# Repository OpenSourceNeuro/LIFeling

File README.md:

<p align="left">

<h1 align="center"> LIFeling </h1></p>
<h3 align="center">  An analog LIF/AdEx “silicon neuron” for teaching & exploration</h3></p>
<p align="center"><h6 align="right">developed by M.J.Y. Zimmermann, A. Koumoundourou</h6></p>

<br></br>

## What is LIFeling
<div>
<p style='text-align: justify;'>
LIFeling is a low-cost, through-hole–friendly analog circuit that emulates a spiking neuron in real time. It implements the Leaky Integrate-and-Fire (LIF) and Adaptive Exponential Integrate-and-Fire (AdEx) dynamics using op-amps, RC networks, comparators, and simple transistor/MOSFET logic.

<p style='text-align: justify;'>
Students can turn knobs (capacitance, leak, synaptic gains, adaptation, threshold, reset) and immediately see how membrane voltage and spikes change—just like a patch-clamp demo, but on an interactive PCB.
</p>

<p style='text-align: justify;'>
LIFeling lives alongside our digital <a href="https://github.com/OpenSourceNeuro/Spikeling">Spikeling</a>: project; where Spikeling runs code, LIFeling is purely analog, making the math–to–hardware mapping very explicit. (For background on AdEx/LIF and neuromorphic “silicon neurons”, <a href="https://www-sop.inria.fr/members/Mathieu.Desroches/teaching/MTSN/Articles/Brette_Gertsner_JNeurophysiol_2005.pdf?utm_source=chatgpt.com">See the references</a>).
</p>

<p style='text-align: justify;'>

This project is licensed under the [GNU General Public License v3.0](https://github.com/OpenSourceNeuro/Spikeling-V2/blob/main/LICENSE)<br>
The hardware is licensed under the [CERN OHL v1.2](https://github.com/OpenSourceNeuro/Spikeling-V2/blob/main/PCB%20-%202.2c/LICENSE)
</p>
</div>

<br>

***

## Objectives
- **Pedagogy** first: Make classical neuron equations tangible with knobs, LEDs, and BNC/TTL I/O so learners can fit parameters from data and build intuition.

- **Open, repairable, reproducible**: THT-preferred BOM where possible; common op-amps (e.g., MCP6004), LM339-class comparators, simple passives; documented test procedures.

- **Immediate feedback**: Real-time dynamics without sampling/latency; scope-friendly nodes for Vm, synaptic currents, threshold comparator, adaptation current.

- **Bridging models**: Start with LIF; switch in AdEx features (exp spike term + adaptation) to show how richer behaviours emerge with just a few components.

- **Teaching exercises**: Provide ready-to-run lab activities (τm measurement, I–F curves, refractory period, synaptic summation, adaptation fitting, noise & reliability). (See Exercises below.)

- **Interoperability**: Optional headers/IO for stimulus/recording from microcontrollers (ESP32/Arduino) and classroom oscilloscopes.

## The models LIFeling implements

#### 1) Leaky Integrate-and-Fire (LIF)

```math
C_m * dV/dt = -g_L * (V - E_L) + I_syn(t) + I_inj(t) - w(t)
```

If V >= V_th  ⇒  V ← V_reset  and hold for τ_ref

with synaptic drive typically modeled as:

```math
I_syn(t) = Σ_i g_i(t) * (E_i - V)
```

LIF captures integration, leakage, threshold, reset, and refractory with minimal parameters.

### Adaptive Exponential Integrate-and-Fire (AdEx)

```math
C_m * dV/dt = -g_L * (V - E_L)
              + g_L * Δ_T * exp((V - V_T)/Δ_T)
              - w
              + I_syn(t) + I_inj(t)

τ_w * dw/dt = a * (V - E_L) - w

If V >= V_spike  ⇒  V ← V_reset  and  w ← w + b
```

AdEx adds a soft, exponential spike-initiation term and an adaptation state w, reproducing rich firing patterns with few parameters.

- Further reading: Brette & Gerstner 2005 (AdEx); Dayan & Abbott 2001 (LIF fundamentals); Indiveri et al. 2011 (neuromorphic neuron circuits).

## Circuit ↔ equation map

| Equation term | Biological meaning | Circuit element(s) | What to adjust / observe |
|---|---|---|---|
| `C_m` | Membrane capacitance (area/biophysics) | Selectable capacitor bank; front-panel selector | Larger `C_m` → slower `V_m` dynamics; measure a step response to estimate `τ_m = C_m / g_L`. |
| `g_L`, `E_L` | Leak conductance & resting potential | Potentiometer or resistor ladder to ground/bias; optional reference sets `E_L` | Increasing `g_L` lowers input resistance and shortens `τ_m`; trimming `E_L` shifts the baseline. |
| `I_syn = Σ g_i(t) · (E_i − V)` | Synaptic drive (EPSC/IPSC) with reversal | 4× synapse shapers (RC) with gain/polarity pots; bias selects excitatory vs inhibitory | Temporal summation, shunting inhibition; switch time constants (fast/slow) to compare PSP shapes. |
| `Δ_T`, `V_T` | Spike-onset sharpness & soft threshold (AdEx) | Exponential I–V subcircuit (diode/transconductance shaping) feeding the membrane node | Increase `Δ_T` for smoother onset; adjust `V_T` to shift effective threshold and excitability. |
| `w`, `a`, `b`, `τ_w` | Adaptation current and kinetics | Slow RC + transconductance; spike-triggered charge increment into `w` | Fit `a`, `b`, `τ_w` from step protocols; observe spike-frequency adaptation and after-spike effects. |
| Spike detect & reset | Action potential event and absolute refractory | LM339-class comparator → MOSFET/analog switch clamp to `V_reset`; monostable sets `τ_ref` | Tune `V_th`, `V_reset`, `τ_ref`; verify with ISI histograms and two-pulse tests. |
| `I_inj` | Current clamp / external stimulus | BNC/3.5 mm input, on-board button, or photodiode path | Use steps/ramps/noise to probe `f–I` curves, threshold, reliability, and dynamic range. |

## Biological correspondence: what’s faithful vs abstracted

Faithful: passive membrane (R–C), synaptic time courses (first-order), EPSP/IPSP summation, threshold/reset phenomenology, refractory period, spike-frequency adaptation.

Abstracted: no detailed action-potential waveform (we model its effect via threshold/reset); ion-channel kinetics are lumped into **g_L**, the exponential term, and **w** rather than Hodgkin–Huxley-style gates.

Optional background: when teaching resting potentials and synaptic reversal, connect channel-specific reversal potentials **E_i** to Nernst/GHK equations (see References).

## Front-panel controls (typical)

**Membrane**: C_m selector, Leak pot (g_L), E_L trim.

**Synapses (×4)**: Gain pot, Polarity switch (E/I), τ_s switch (fast/slow).

**AdEx**: V_T, Δ_T trims (soft threshold), Adaptation (a, b, τ_w) pots.

**Spiking**: V_th, V_reset, τ_ref trims; Spike LED.

**I/O**: Vm out (scope), Spike out (TTL), Stim in (BNC/3.5 mm), light-sensor jack.

Start with τ_m ≈ 5–100 ms and spike thresholds ~0.8–1.8 V relative to your virtual ground (adjust for your supply).

## Quick start (bench)

Power & baseline. Power the board; set all gains mid-range; choose C_m, set leak mid.

Wire the scope. CH1 = Vm; CH2 = Spike TTL.

Elicit spikes. Inject a 0.5–2 s current step; adjust threshold/reset until regular spiking appears.

Add small Δ_T and adaptation (τ_w ≈ 200–500 ms). Watch firing adapt down.

Play with synapses. Use fast EPSPs and slower IPSPs to demonstrate temporal summation and shunting inhibition.

## Suggested classroom exercises

**Measure membrane time constant τ_m.**
Inject a small subthreshold step; fit V(t) = E_L + ΔV*(1 - exp(-t/τ_m)). Recover C_m or g_L and compare to knob settings.

**I–F (f–I) curve & rheobase.**
Ramp I_inj and record firing rate. Fit slope and rheobase; show how g_L and C_m change slope/offset.

**Refractory period.**
Deliver two pulses separated by Δt; find minimum Δt producing two spikes; compare to τ_ref.

**Synaptic summation and shunting.**
Pair an EPSP with a near-coincident IPSP; demonstrate divisive gain control by increasing inhibitory conductance (shunting).

**Spike-frequency adaptation (AdEx).**
Step-current protocol; fit a, b, τ_w from the early/late rates and the post-spike adaptation jump.

**Soft vs hard threshold.**
Compare LIF (hard V_th) to AdEx (Δ_T > 0). Show smoother onset and different ISI variability with AdEx.

**Noise & reliability.**
Add small noise to I_inj; plot spike-time jitter vs g_L. Discuss reliability/variability trade-offs.

**Analog vs digital (optional).**
Recreate one exercise on a microcontroller neuron (e.g., Izhikevich) and compare dynamics, latency, and parameter identifiability.

## Acknowledgments

Foundation: This project is based on Lu.i — https://github.com/giant-axon/lu.i-neuron-pcb

Thanks to the neuromorphic-hardware community for decades of open designs and teaching inspiration.

## References & further reading

AdEx model — Brette, R. & Gerstner, W. (2005). Adaptive Exponential Integrate-and-Fire Model as an Effective Description of Neuronal Activity. Journal of Neurophysiology, 94(5), 3637–3642. https://doi.org/10.1152/jn.00686.2005

LIF & synapses — Dayan, P. & Abbott, L. F. (2001). Theoretical Neuroscience. MIT Press. (See chapters on LIF, synapses, and I–F curves.)

Neuromorphic circuits — Indiveri, G., Linares-Barranco, B., et al. (2011). Neuromorphic Silicon Neuron Circuits. Frontiers in Neuroscience, 5:73. https://doi.org/10.3389/fnins.2011.00073
 (Open access)

Spiking for teaching (digital reference) — Baden, T., James, B., et al. (2018). Spikeling: a low-cost hardware implementation of a spiking neuron for neuroscience teaching and outreach. PLOS Biology. https://doi.org/10.1371/journal.pbio.2006760

Ion channels & reversals (background) — Hille, B. (2001). Ion Channels of Excitable Membranes (3rd ed.). Sinauer. (Nernst/GHK chapters)

## Contributing

Issues and PRs welcome!
When reporting results, please include:

Scope captures (Vm & Spike TTL),

Knob settings (Cm, gL, ΔT, Vth, Vreset, τref, a, b, τw),

The stimulus used (step amplitude, duration, ramp slope, synaptic timing),

Supply voltage and any modifications to the reference design.

## FAQ

Is this a “real” action potential?
No—the analog spike is implicit (threshold/reset). That’s by design and matches reduced-model pedagogy.

Why analog instead of a microcontroller?
Zero-latency dynamics and a literal circuit-to-equation mapping you can probe with a scope—excellent for intuition building.

Can I add more biology?
Yes: add synapse types (different τ_s), noise sources, or a second compartment. Use the AdEx literature and neuromorphic reviews as guidance.

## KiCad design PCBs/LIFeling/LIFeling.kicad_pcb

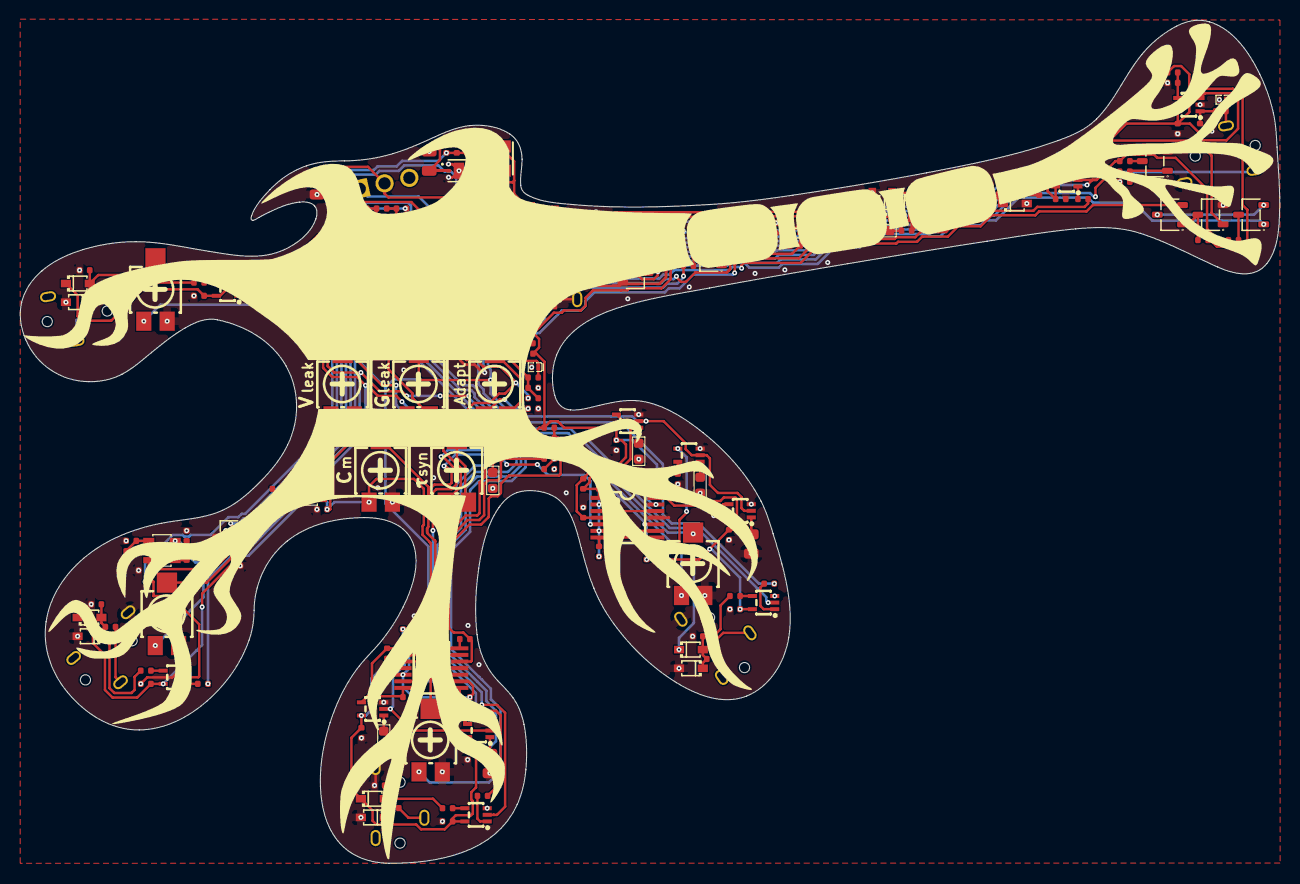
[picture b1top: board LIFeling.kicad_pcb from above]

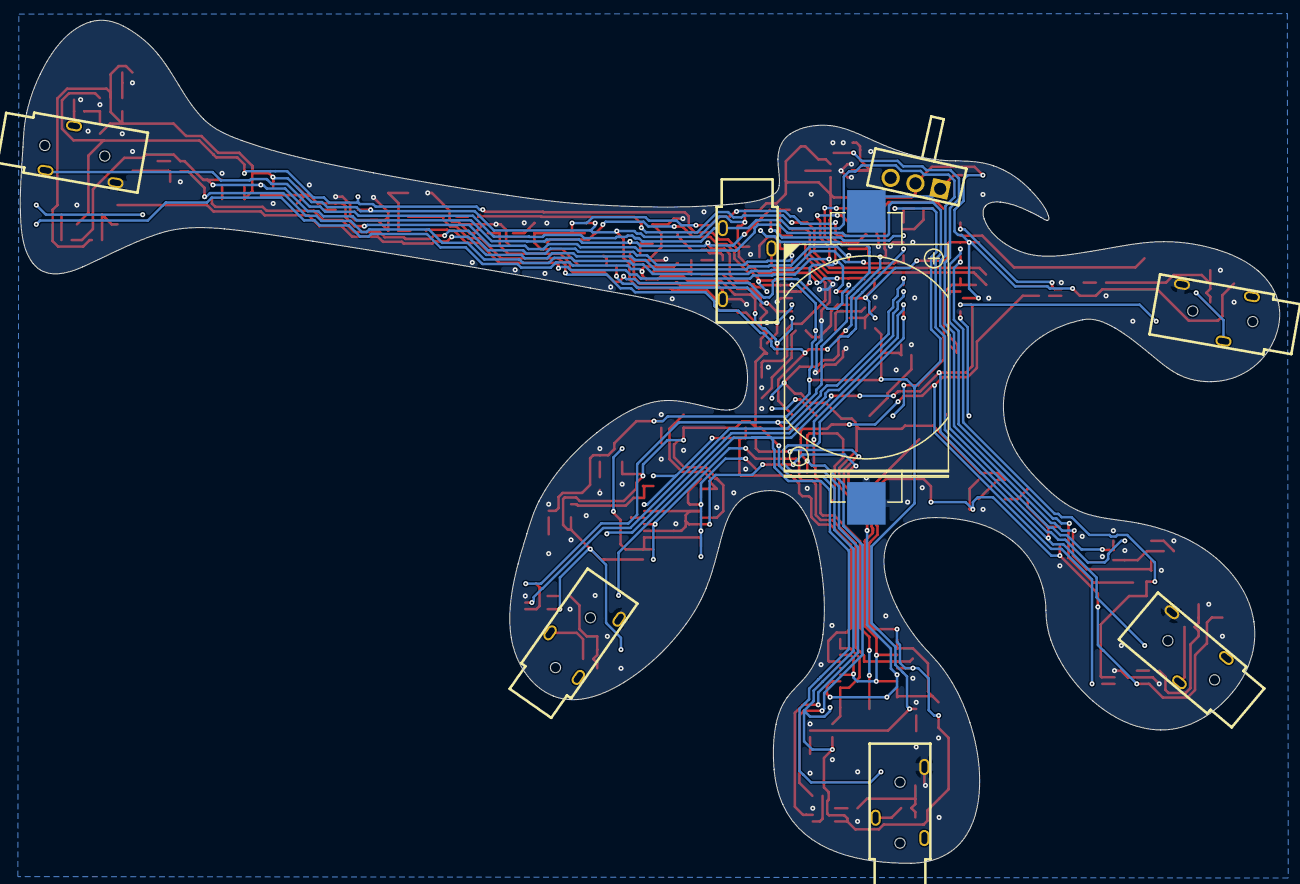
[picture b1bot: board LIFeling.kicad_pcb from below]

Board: 2 copper layers, 124.1 x 83.0 mm, 215 parts (8 on the bottom side), 106 nets.

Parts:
BT1: type="R" model="Battery_Cell" lib=""; BAT-TH_CR2032-BS-6-1
C1, C2, C9, C26, C30: 10uF; C_0805
C3, C4, C5, C6, C7, C8, C12, C14, C15, C17, C19, C21, C23, C25, C27, C32, C34, C35, C36, C37, C40, C41, C42: 100nF; C_0402
C10: 22uF; C_0805
C11, C33: 1uF; C_0402
C13, C28, C39: 100pF; C_0402
C16: 22nF; C_0402
C18: 470nF; C_0603
C20, C29: 1uF; C_0603
C22: 2.2uF; C_0603
C24: 4.7uF; C_0805
C31: 10nF; C_0402
C38: 220nF; C_0603
D1, D19: TPD1E05U06DPYT; X1SON-2_L1.0-W0.6-P0.65-RD-1
D2, D3, D10, D11, D12, D13, D14, D15, D16, D17, D21, D22: BAT54WS L9; SOD-323_L1.8-W1.3-LS2.5-RD
D4, D5, D7: 1N4148WS; SOD-323_L1.8-W1.3-LS2.5-RD-1
D6, D8, D20: RB521S30T1G; SOD-523_L1.2-W0.8-LS1.6-RD
D9: 19-237/R6GHBHC-A01/2T; LED-SMD_4P-L1.6-W1.6-19-237A-BHR6GHC-A01-2T
D18: TPD1E05U06DPYT; X1SON-2_L1.0-W0.6-P0.65-RD
H1, H2, H3, H4, H5, H6: MountingHole; MountingHole_2.2mm_M2
J1: Stim_Ext; AUDIO-SMD_HX-PJ-320A-3P-DIP
J2: Axon_Output; AUDIO-SMD_HX-PJ-320A-3P-DIP
J3: Syn1_Input; AUDIO-SMD_HX-PJ-320A-3P-DIP
J4: Syn2_Input; AUDIO-SMD_HX-PJ-320A-3P-DIP
J5: Syn3_Input; AUDIO-SMD_HX-PJ-320A-3P-DIP
J6: Syn4_Input; AUDIO-SMD_HX-PJ-320A-3P-DIP
L1: 2.2uH; IND-SMD_L3.0-W3.0_SMNR3015
Q1, Q3, Q4, Q5, Q6, Q7: BSS138; SOT-23-3_L2.9-W1.6-P1.90-LS2.8-BR
Q2, Q8: MMBT3904; SOT-23-3_L2.9-W1.6-P1.90-LS2.8-BR
R1: 10Ω; R_0402
R2: 220Ω; R_0402
R3, R16, R37, R46, R52, R60, R64, R82: 10kΩ; R_0402
R4, R8, R9, R11, R15, R17, R18, R19, R20, R21, R22, R24, R27, R30, R33, R38, R42, R43, R48, R49, R51, R55, R59, R65, R68, R72, R76, R80, R88, R92, R95, R96, R97: 100kΩ; R_0402
R5, R6, R13, R14, R58: 220kΩ; R_0402
R7: 20kΩ; R_0402
R10: 56kΩ; R_0402
R12, R23, R25, R26, R28, R29, R31, R32, R34, R50, R57, R83, R84, R85, R86, R90: 1MΩ; R_0402
R35, R67, R71, R75, R79, R91: 1kΩ; R_0402
R36: 2.2MΩ; R_0402
R39, R47, R53, R66, R69, R70, R73, R74, R77, R78, R81: 22kΩ; R_0402
R40, R54, R89: 100Ω; R_0402
R41, R44, R93, R94: 200kΩ; R_0402
R45: 330kΩ; R_0402
R56: 270kΩ; R_0402
R61, R62, R63: 2kΩ; R_0402
R87: 47kΩ; R_0402
RV1, RV3, RV4, RV5: 100kΩ; RES-ADJ-SMD_G43BT
RV2: 50kΩ; RES-ADJ-SMD_G43BT
RV6, RV7, RV8, RV9: 1MΩ; RES-ADJ-SMD_G43BT
SW1: K3-1260D-L1; SW-TH_K3-1260D-L1
U1, U2, U3: MCP6004T-I/ST; TSSOP-14_L5.0-W4.4-P0.65-LS6.4-BL
U4, U5, U6: TLV7044PWR; TSSOP-14_L5.0-W4.4-P0.65-LS6.4-BL
U7: TPS610995DRVR; WSON-6_L2.0-W2.0-P0.65-TL-EP
U8, U22: TLV9001IDBVR; SOT-23-5_L3.0-W1.7-P0.95-LS2.8-BR
U9, U10, U11, U12, U13, U14, U15, U16, U17, U18, U20: TS5A3166DCKR; SC-70-5_L2.1-W1.3-P0.65-LS2.1-BR
U19: TLV7031DCKR; SC-70-5_L2.1-W1.3-P0.65-LS2.2-BR
U21: REF3020AIDBZR; SOT-23-3_L3.0-W1.7-P0.95-LS2.9-BR

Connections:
+BATT: BT1.1 (+), C1.1, SW1.1
/AP_Gate: Q1.1 (G), R36.2, R37.2, U6.14 (OUTD)
/Adapt: R44.2, R45.1, U2.14 (VOUTD)
/Adapt_Base: Q2.1, R47.1, R48.1
/Adapt_Current_Sink: Q2.3, R46.2
/Adapt_Kick_Drive: C29.2, U2.1 (VOUTA), U2.2 (VINA-)
/Reset_Gated_Drive: Q6.3 (D), R60.1
/Reset_Injection_Drive: Q5.2 (S), U2.6 (VINB-), U2.7 (VOUTB)
/Reset_Injection_Enable: Q4.3 (D), Q5.1 (G), R59.2
/Reset_Switch_Mid: Q5.3 (D), Q6.2 (S)
/Reset_Timer_Discharge: Q3.3 (D), R54.1
/Rising_AP: C31.2, D8.2 (A), R49.1
/V_Leak_ref: RV1.2, U3.3 (VINA+)
/V_Syn_Drive: R86.2, R87.1, U1.14 (VOUTD)
/Vkick: C29.1, D4.1 (C), D5.2 (A), R39.2
AP: C31.1, Q1.3 (D), Q3.1 (G), R38.2, U2.3 (VINA+)
GNDREF: BT1.2 (-), C1.2, C2.2, C3.1, C4.1, C5.1, C6.1, C7.1, C8.1, C9.2, C10.1, C11.2, C12.2, C13.2, C14.2, C15.2, C16.1, C17.2, C18.2, C19.2, C20.2, C21.2, C22.2, C23.2, C24.2, C25.2, C26.2, C27.2, C28.1, C30.1, C32.2, C33.1, C34.2, C35.2, C36.2, C37.2, C38.1, C39.2, C40.2, C41.1, C42.1, D1.2 (GND), D3.2 (A), D4.2 (A), D7.2 (A), D11.2 (A), D13.2 (A), D15.2 (A), D17.2 (A), D18.2 (GND), D19.2 (GND), D20.2 (A), D22.2 (A), J1.3, J2.3, J3.3, J4.3, J5.3, J6.3, Q1.2 (S), Q2.2, Q3.2 (S), Q4.2 (S), Q7.2 (S), Q8.2, R4.1, R6.1, R8.2, R10.1, R12.1, R14.1, R21.2, R39.1, R40.2, R41.1, R48.2, R49.2, R50.1, R58.1, R65.2, R68.1, R72.1, R76.1, R80.1, RV1.1, RV4.1, RV6.1, RV7.1, RV8.1, RV9.1, U1.11 (VSS), U2.11 (VSS), U3.11 (VSS), U4.11 (VEE), U5.11 (VEE), U6.11 (VEE), U7.1 (GND), U7.3 (FB), U7.7 (PowerPad), U8.2 (V-), U9.3 (GND), U10.3 (GND), U11.3 (GND), U12.3 (GND), U13.3 (GND), U14.3 (GND), U15.3 (GND), U16.3 (GND), U17.3 (GND), U18.3 (GND), U19.2 (GND), U20.3 (GND), U21.3 (GND), U22.2 (V-)
unnamed: D6.2 (A), R45.2
unnamed: D9.3 (B-), R61.2
unnamed: D9.2 (G-), R62.2
unnamed: D9.1 (R-), R63.2
unnamed: D10.2 (A), D11.1 (K), R67.2, R68.2, R69.2
unnamed: D12.2 (A), D13.1 (K), R71.2, R72.2, R73.2
unnamed: D14.2 (A), D15.1 (K), R75.2, R76.2, R77.2
unnamed: D16.2 (A), D17.1 (K), R79.2, R80.2, R81.2
unnamed: Q7.3 (D), R61.1, R62.1
unnamed: Q8.1, R64.1, R65.1
unnamed: Q8.3, R63.1
unnamed: R35.1, RV2.1
unnamed: R40.1, RV3.3
unnamed: R82.2, RV5.1, RV5.2
unnamed: RV7.2, U1.5 (VINB+)
unnamed: R83.2, R84.2, U1.12 (VIND+)
unnamed: R85.2, R86.1, U1.13 (VIND-)
unnamed: RV6.2, U1.3 (VINA+)
unnamed: R41.2, R42.1, U2.12 (VIND+)
unnamed: R43.1, R44.1, U2.13 (VIND-)
unnamed: RV8.2, U3.10 (VINC+)
unnamed: RV9.2, U3.12 (VIND+)
unnamed: R92.2, R93.2, U6.5 (INB+)
unnamed: R94.2, R95.2, U6.6 (INB-)
unnamed: R56.1, R57.1, R58.2, U6.10 (INC+)
unnamed: C33.2, R53.2, R54.2, U6.9 (INC-)
unnamed: L1.2, U7.5 (SW)
unnamed: C10.2, R1.1, U7.2 (VOUT)
unnamed: C18.1, U9.1 (NO)
unnamed: C20.1, U10.1 (NO)
unnamed: C22.1, U11.1 (NO)
unnamed: C24.1, U12.1 (NO)
unnamed: C26.1, U13.1 (NO)
unnamed: R52.1, U14.1 (NO)
unnamed: R67.1, U15.4 (IN)
unnamed: R66.1, U15.1 (NO)
unnamed: R71.1, U16.4 (IN)
unnamed: R70.1, U16.1 (NO)
unnamed: R75.1, U17.4 (IN)
unnamed: R74.1, U17.1 (NO)
unnamed: R79.1, U18.4 (IN)
unnamed: R78.1, U18.1 (NO)
unnamed: R88.2, R89.1, U19.1 (OUT)
unnamed: R16.1, U20.1 (NO)
Peak_Window: Q4.1 (G), R51.2, U6.1 (OUTA), U14.4 (IN), U19.3 (IN+), U20.4 (IN)
Reset_Window: Q6.1 (G), Q7.1 (G), R55.2, R57.2, U6.8 (OUTC)
S0: R22.2, R23.2, U4.1 (OUTA), U9.4 (IN)
S1: R24.2, R25.2, R26.2, U4.7 (OUTB), U4.8 (OUTC), U10.4 (IN)
S2: R27.2, R28.2, R29.2, U5.1 (OUTA), U5.7 (OUTB), U11.4 (IN)
S3: R30.2, R31.2, R32.2, U5.8 (OUTC), U5.14 (OUTD), U12.4 (IN)
S4: R33.2, R34.2, U4.14 (OUTD), U13.4 (IN)
Spike_Out: D18.1 (I/O), J2.2, R89.2
Spike_Pulse: D8.1 (C), D20.1 (C), R50.2, U6.2 (INA+)
Stimulus_Ext: D19.1 (I/O), J1.2, R91.1
Syn1_Spike: J3.2, R69.1
Syn2_Spike: J4.2, R73.1
Syn3_Spike: J5.2, R77.1
Syn4_Spike: J6.2, R81.1
T1: R20.2, R21.1, R23.1, R25.1, U4.2 (INA+), U4.6 (INB-)
T2: R19.2, R20.1, R26.1, R28.1, U4.10 (INC+), U5.3 (INA-)
T3: R18.2, R19.1, R29.1, R31.1, U5.5 (INB+), U5.9 (INC-)
T4: R17.2, R18.1, R32.1, R34.1, U4.13 (IND−), U5.12 (IND+)
VDD: C2.1, C3.2, C4.2, C5.2, C6.2, C7.2, C8.2, C9.1, C17.1, C19.1, C21.1, C23.1, C25.1, C27.1, C32.1, C34.1, C35.1, C36.1, C37.1, C40.1, C41.2, C42.2, D2.1 (K), D9.4 (+), D10.1 (K), D12.1 (K), D14.1 (K), D16.1 (K), D21.1 (K), L1.1, R11.1, R13.2, R17.1, R22.1, R24.1, R27.1, R30.1, R33.1, R37.1, R38.1, R51.1, R53.1, R55.1, R56.2, R59.1, R88.1, R96.1, RV4.3, SW1.2, U1.4 (VDD), U2.4 (VDD), U3.4 (VDD), U4.4 (VCC), U5.4 (VCC), U6.4 (VCC), U7.4 (EN), U7.6 (VIN), U9.5 (V+), U10.5 (V+), U11.5 (V+), U12.5 (V+), U13.5 (V+), U14.5 (V+), U15.5 (V+), U16.5 (V+), U17.5 (V+), U18.5 (V+), U19.5 (VCC), U20.5 (V+), U21.1 (IN), U22.5 (V+)
VREF_1V024: R7.2, R9.1, R85.1, R90.1, R94.1, RV5.3, U22.1 (OUT), U22.4 (IN-)
VREF_1V024_RAW: R5.1, R6.2, U22.3 (IN+)
VREF_2V048: C15.1, R5.2, RV6.3, RV7.3, RV8.3, RV9.3, U3.5 (VINB+), U21.2 (OUT)
V_Boost: C11.1, C12.1, C14.1, R1.2, U8.5 (V+)
V_Leak: R43.2, RV2.3, U3.1 (VOUTA), U3.2 (VINA-)
V_Leak_Ref_Max: RV1.3, U3.6 (VINB-), U3.7 (VOUTB)
V_Logic_Mid: R13.1, R14.2, U19.4 (IN-)
V_Peak_Drive: R16.2, R52.2, U2.8 (VOUTC), U2.9 (VINC-)
V_Peak_Ref: R11.2, R12.2, U2.10 (VINC+)
V_Reset_Ref: R9.2, R10.2, U2.5 (VINB+)
V_Stim_Cmd: C39.1, R90.2, R91.2, R93.1
V_Stim_Drive: R95.1, R96.2, R97.1, U6.7 (OUTB)
V_Syn1_Set: U1.1 (VOUTA), U1.2 (VINA-), U15.2 (COM)
V_Syn2_Set: U1.6 (VINB-), U1.7 (VOUTB), U16.2 (COM)
V_Syn3_Set: U3.8 (VOUTC), U3.9 (VINC-), U17.2 (COM)
V_Syn4_Set: U3.13 (VIND-), U3.14 (VOUTD), U18.2 (COM)
V_Syn_State: C38.2, R66.2, R70.2, R74.2, R78.2, R82.1, R83.1
V_Threshold: R7.1, R8.1, R36.1, U6.3 (INA-), U6.12 (IND+)
Vm_Display_In: C16.2, D21.2 (A), D22.1 (K), R15.1, U8.3 (IN+), U20.2 (COM)
Vm_Ext: C13.1, D1.1 (I/O), J1.1, J2.1, R2.2
Vm_FB: R3.1, R4.2, U8.4 (IN-)
Vm_Int: C28.2, D2.2 (A), D3.1 (K), R15.2, R35.2, R42.2, R46.1, R60.2, R64.2, R84.1, R87.2, R92.1, R97.2, RV2.2, U6.13 (IND−), U9.2 (COM), U10.2 (COM), U11.2 (COM), U12.2 (COM), U13.2 (COM), U14.2 (COM)
Vm_Out_DRV: R2.1, R3.2, U8.1 (OUT)
Vsel: RV4.2, U4.3 (INA-), U4.5 (INB+), U4.9 (INC-), U4.12 (IND+), U5.2 (INA+), U5.6 (INB-), U5.10 (INC+), U5.13 (IND−)
Vw: C30.2, D5.1 (C), D6.1 (C), D7.1 (C), RV3.1, RV3.2, U1.10 (VINC+)
Vw_buff: R47.2, U1.8 (VOUTC), U1.9 (VINC-)

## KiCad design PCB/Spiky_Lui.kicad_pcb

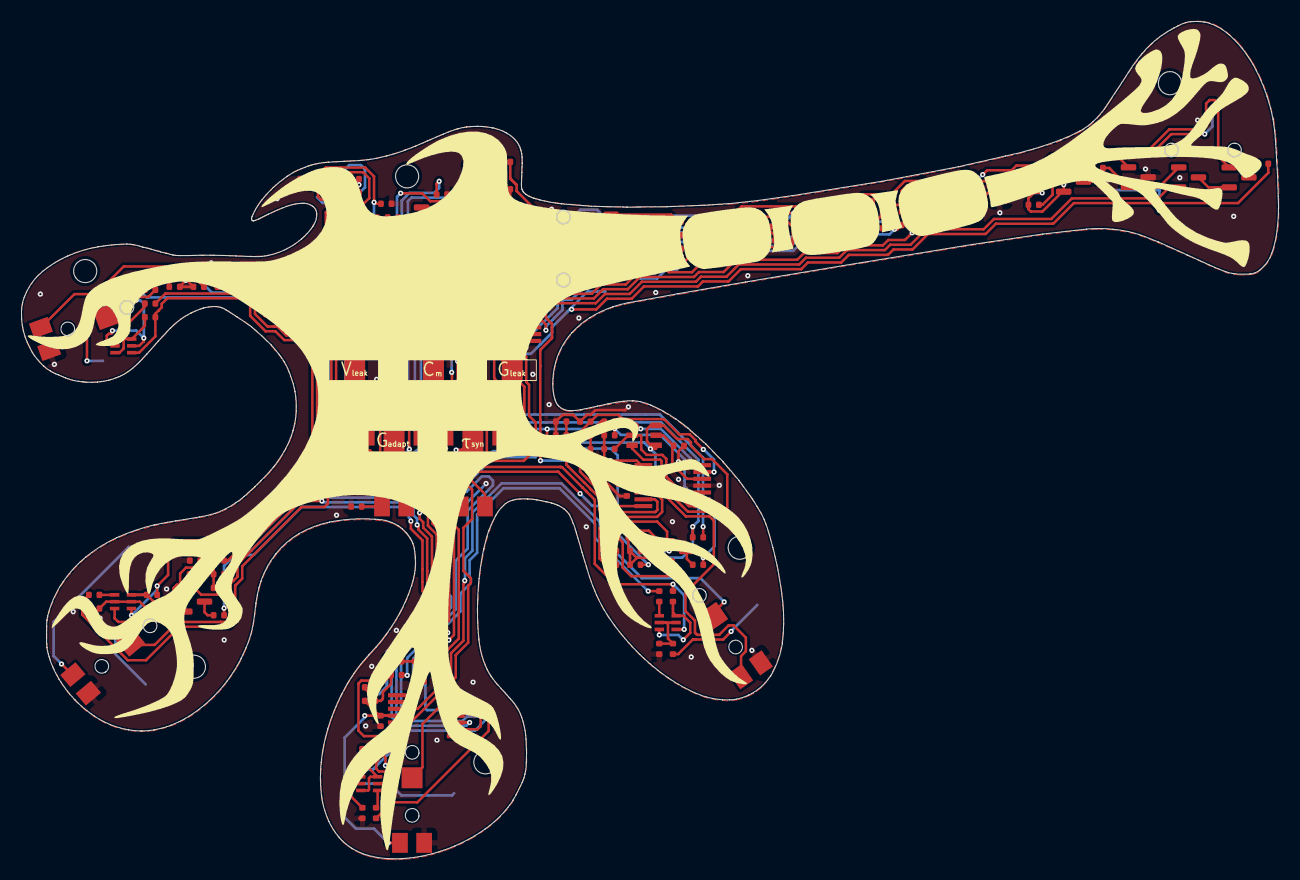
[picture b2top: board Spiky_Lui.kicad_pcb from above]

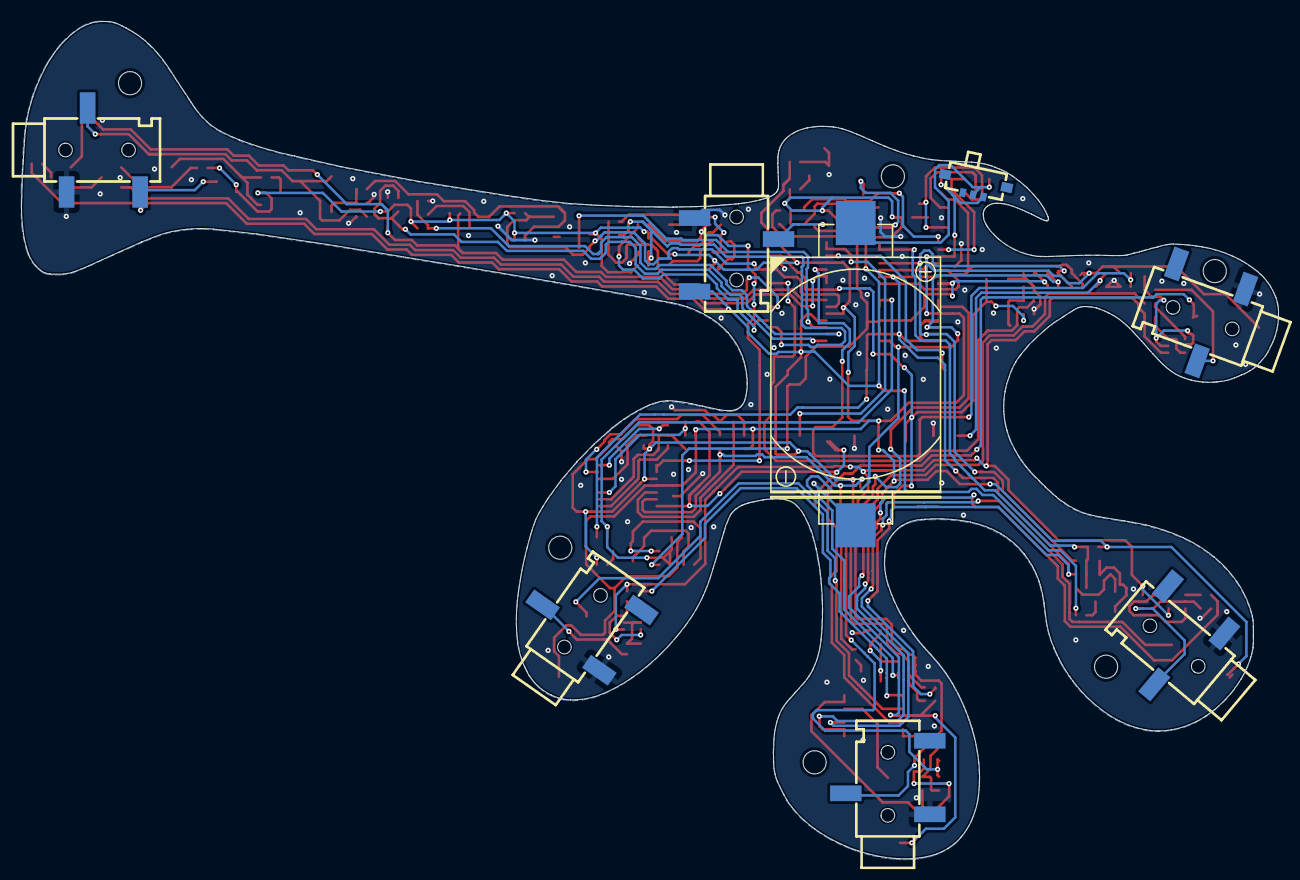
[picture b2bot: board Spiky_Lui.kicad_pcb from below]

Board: 2 copper layers, 119.7 x 79.7 mm, 166 parts (8 on the bottom side), 99 nets.

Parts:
BT1: type="R" model="Battery_Cell" lib=""; BAT-TH_CR2032-BS-6-1
C2: 470nF; C_0402
C3, C14, C16, C17: 1uF; C_0402
C4: 2.2uF; C_0402
C5: 4.7uF; C_0402
C6, C8, C18: 10uF; C_0402
C9, C10, C11, C12, C15, C19, C20: 100nF; C_0402
C13: 10nF; C_0402
D1: 1N4148W; SOD-123_L2.8-W1.8-LS3.7-RD
D2: 19-237/R6GHBHC-A01/2T; LED-SMD_4P-L1.6-W1.6-19-237A-BHR6GHC-A01-2T
D3, D4, D5: 1N4148WS; D_SOD-323
H1, H2, H3, H4, H5, H6: MountingHole; MountingHole_2.2mm_M2
J1: Oscilloscope Jack; AUDIO-SMD_PJ-320B
J2: Axon Output; AUDIO-SMD_PJ-320B
J3: Syn1 Input; AUDIO-SMD_PJ-320B
J4: Syn2 Input; AUDIO-SMD_PJ-320B
J5: Syn3 Input; AUDIO-SMD_PJ-320B
J6: Syn4 Input; AUDIO-SMD_PJ-320B
Q1, Q2, Q3, Q6, Q7, Q16, Q17, Q18, Q19, Q20: N_MOSFET; SOT-23
Q4, Q5: P_MOSFET; SOT-23
Q8: SI3552DV-T1-E3; TSOP-6_L3.0-W1.5-P0.95-BL
Q9, Q10, Q11, Q12: SI1926DL-T1-E3; SOT-363-6_L2.0-W1.3-P0.65-LS2.1-BL
Q13, Q14: MMBT2222A; Q_SOT-23
Q15: MMBT3904; SOT-23
R1: 6.8kΩ; R_0402
R2, R3: 1kΩ; R_0402
R4: 2kΩ; R_0402
R5, R7, R56, R57, R58: 220kΩ; R_0402
R6, R34, R35: 47kΩ; R_0402
R8, R60, R62, R63: 10kΩ; R_0402
R9, R15, R18, R22, R23, R31, R32, R33, R36: 22kΩ; R_0402
R10, R12, R14, R19, R21, R24, R28, R29, R30, R40, R44, R48, R52, R59, R65, R66, R68, R70, R72, R76, R79, R80, R83, R86, R89, R92: 100kΩ; R_0402
R11, R13, R67, R69, R71, R73, R74, R75, R77, R78, R81, R84, R87, R90, R93: 1MΩ; R_0402
R16: 1Ω; R_0402
R17: 27kΩ; R_0402
R20, R55: 4.7kΩ; R_0402
R25, R26, R27, R39, R41, R42, R43, R45, R46, R47, R49, R50, R51, R53, R54: 100Ω; R_0402
R37, R38: 2.4kΩ; R_0402
R61: 300kΩ; R_0402
R64: 220Ω; R_0402
R82, R85, R88, R91, R94: 10Ω; R_0402
RV1, RV5, RV6, RV7, RV8: 100kΩ; RES-ADJ-SMD_G43BT
RV2, RV3, RV9: 50kΩ; RES-ADJ-SMD_G43BT
RV4: 10kΩ; RES-ADJ-SMD_G43BT
SW1: SW_SPDT; SW-SMD_SSAJ120100
U1, U2, U3: MCP6004T-I/ST; TSSOP-14_L5.0-W4.4-P0.65-LS6.4-BL
U4, U5, U6: LM339; TSSOP-14_L5.0-W4.4-P0.65-LS6.4-BL

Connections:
+0.375V: R1.2, R2.1, U1.5 (VINB+)
+2V: R3.2, R4.1, RV1.3
+BATT: BT1.1 (+), C8.1, SW1.2 (B)
/Reset_Current_Injection: Q6.2 (S), U1.6 (VINB-), U1.7 (VOUTB)
/Rising_AP: C13.2, D1.2 (A), R10.1
/V_Leak: RV2.3, U1.1 (VOUTA), U1.2 (VINA-)
/V_Spike_Threshold: R56.2, R57.1, R58.1, U4.10 (-)
/V_Threshold: R5.2, R6.1, R7.1, U4.5 (+)
/V_ref: RV1.2, U1.3 (VINA+)
/Vkick: C16.2, D3.1, D4.2, R22.1
/Vw: C17.2, D4.1, D5.1, RV3.1, RV3.2, U1.12 (VIND+)
/Vw_buf: R23.1, U1.13 (VIND-), U1.14 (VOUTD)
AP: C13.1, Q1.3 (D), Q2.1 (G), R9.2
GNDREF: BT1.2 (-), C2.2, C3.2, C4.2, C5.2, C6.2, C8.2, C9.2, C10.2, C11.2, C12.2, C14.2, C15.2, C17.1, C19.2, C20.2, D3.2, D5.2, J1.1, J2.1, J3.1, J4.1, J5.1, J6.1, Q1.2 (S), Q2.2 (S), Q3.2 (S), Q5.3 (D), Q13.2 (E), Q14.2 (E), Q15.2 (E), R2.2, R4.2, R6.2, R10.2, R11.2, R18.2, R22.2, R24.1, R26.2, R32.2, R36.2, R38.2, R40.1, R44.1, R48.1, R52.1, R57.2, R66.2, RV1.1, RV5.1, RV6.1, RV7.1, RV8.1, RV9.1, U1.11 (VSS), U2.11 (VSS), U3.11 (VSS), U4.12 (V-), U5.12 (V-), U6.12 (V-)
unnamed: D2.4 (+), R64.2
unnamed: D2.2 (G-), D2.3 (B-), Q14.3 (C)
unnamed: D2.1 (R-), Q13.3 (C)
unnamed: Q2.3 (D), R16.2
unnamed: Q3.3 (D), R12.1
unnamed: Q4.1 (G), Q5.1 (G), R12.2, R13.2
unnamed: Q6.3 (D), Q7.2 (S)
unnamed: Q7.3 (D), R21.1
unnamed: Q8.1 (NG), U2.14 (VOUTD)
unnamed: Q8.5 (NS), R38.1, U2.12 (VIND+)
unnamed: Q8.3 (PG), U2.8 (VOUTC)
unnamed: Q8.2 (PS), R37.2, U2.9 (VINC-)
unnamed: Q9.3 (D2), Q9.6 (D1), R42.1
unnamed: Q9.2 (G1), Q9.5 (G2), R39.2, R40.2
unnamed: Q9.1 (S1), R41.2
unnamed: Q10.3 (D2), Q10.6 (D1), R46.1
unnamed: Q10.2 (G1), Q10.5 (G2), R43.2, R44.2
unnamed: Q10.1 (S1), R45.2
unnamed: Q9.4 (S2), Q10.4 (S2), Q11.4 (S2), Q12.4 (S2), R42.2, R46.2, R50.2, R54.2, R55.1
unnamed: Q11.3 (D2), Q11.6 (D1), R50.1
unnamed: Q11.2 (G1), Q11.5 (G2), R47.2, R48.2
unnamed: Q11.1 (S1), R49.2
unnamed: Q12.3 (D2), Q12.6 (D1), R54.1
unnamed: Q12.2 (G1), Q12.5 (G2), R51.2, R52.2
unnamed: Q12.1 (S1), R53.2
unnamed: Q13.1 (B), R63.2
unnamed: Q14.1 (B), R60.1
unnamed: Q15.1 (B), R23.2, R24.2
unnamed: Q15.3 (C), R25.1
unnamed: Q16.3 (D), R82.2
unnamed: Q16.1 (G), R80.2, R81.1
unnamed: C2.1, Q16.2 (S), R81.2
unnamed: Q17.3 (D), R85.2
unnamed: Q17.1 (G), R83.2, R84.1
unnamed: C3.1, Q17.2 (S), R84.2
unnamed: Q18.3 (D), R88.2
unnamed: Q18.1 (G), R86.2, R87.1
unnamed: C4.1, Q18.2 (S), R87.2
unnamed: Q19.3 (D), R91.2
unnamed: Q19.1 (G), R89.2, R90.1
unnamed: C5.1, Q19.2 (S), R90.2
unnamed: Q20.3 (D), R94.2
unnamed: Q20.1 (G), R92.2, R93.1
unnamed: C6.1, Q20.2 (S), R93.2
unnamed: R26.1, RV3.3
unnamed: R58.2, R59.2, R60.2, R61.1, U4.13
unnamed: C16.1, U1.8 (VOUTC), U1.9 (VINC-)
unnamed: C19.1, R31.2, R32.1, U2.5 (VINB+)
unnamed: C18.2, R34.2, R35.1, RV4.1, RV4.2, U2.7 (VOUTB)
unnamed: R33.2, R34.1, U2.10 (VINC+)
unnamed: R35.2, R36.1, U2.13 (VIND-)
unnamed: R62.1, R63.1, U2.1 (VOUTA), U2.2 (VINA-)
unnamed: RV5.2, U3.5 (VINB+)
unnamed: R41.1, U3.6 (VINB-), U3.7 (VOUTB)
unnamed: RV6.2, U3.10 (VINC+)
unnamed: R45.1, U3.8 (VOUTC), U3.9 (VINC-)
unnamed: RV7.2, U3.12 (VIND+)
unnamed: R49.1, U3.13 (VIND-), U3.14 (VOUTD)
unnamed: RV8.2, U3.3 (VINA+)
unnamed: R53.1, U3.1 (VOUTA), U3.2 (VINA-)
unnamed: R17.2, R18.1, R19.1, U4.7 (+)
unnamed: C14.1, R15.2, R16.1, U4.6 (-)
unnamed: R61.2, R62.2, U4.11 (+)
Peak: Q5.2 (S), Q6.1 (G), R14.2
Reset: Q7.1 (G), R19.2, R20.2, U4.1
S0: R67.2, R68.1, R80.1, U5.2
S1: R71.2, R72.1, R73.2, R83.1, U5.13, U5.14
S2: R74.2, R75.2, R76.1, R86.1, U6.1, U6.2
S3: R77.2, R78.2, R79.1, R89.1, U6.13, U6.14
S4: R69.2, R70.1, R92.1, U5.1
SP: Q1.1 (G), R7.2, R8.2, U1.10 (VINC+), U4.2
Spike: D1.1 (K), J2.2, Q3.1 (G), R11.1
Stimulus_In: J1.2, R27.2
Syn1_Spike: J3.2, R39.1
Syn2_Spike: J4.2, R43.1
Syn3_Spike: J5.2, R47.1
Syn4_Spike: J6.2, R51.1
T1: R65.2, R66.1, R69.1, R78.1, U5.7 (+), U6.11 (+)
T2: R30.2, R65.1, R75.1, U6.5 (+), U6.8 (-)
T3: R29.2, R30.1, R73.1, U5.11 (+), U6.6 (-)
T4: R28.2, R29.1, R67.1, U5.5 (+), U5.8 (-)
VDD: C9.1, C10.1, C11.1, C12.1, C15.1, C20.1, Q4.2 (S), R1.1, R3.1, R5.1, R8.1, R9.1, R13.1, R14.1, R15.1, R17.1, R20.1, R28.1, R31.1, R33.1, R37.1, R56.1, R59.1, R64.1, R68.2, R70.2, R72.2, R76.2, R79.2, RV5.3, RV6.3, RV7.3, RV8.3, RV9.3, SW1.1 (A), U1.4 (VDD), U2.4 (VDD), U3.4 (VDD), U4.3 (V+), U5.3 (V+), U6.3 (V+)
V_Synapses: C18.1, R55.2, RV4.3, U2.6 (VINB-)
Vm: J1.3, J2.3, Q4.3 (D), Q8.4 (PD), Q8.6 (ND), R21.2, R25.2, R27.1, R82.1, R85.1, R88.1, R91.1, R94.1, RV2.1, RV2.2, U2.3 (VINA+), U4.4 (-)
Vsel: R71.1, R74.1, R77.1, RV9.2, U5.4 (-), U5.6 (-), U5.9 (+), U5.10 (-), U6.4 (-), U6.7 (+), U6.9 (+), U6.10 (-)

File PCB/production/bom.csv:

Designator,Footprint,Quantity,Value,LCSC Part #
BT1,BAT-TH_CR2032-BS-6-1,1,"type=""R"" model=""Battery_Cell"" lib=""""",C70377
"C10, C11, C12, C15, C19, C20, C9",C_0402,7,100nF,C1525
C13,C_0402,1,10nF,C15195
"C14, C16, C17, C3",C_0402,4,1uF,C52923
"C18, C6, C8",C_0402,3,10uF,C15525
C2,C_0402,1,470nF,C47339
C4,C_0402,1,2.2uF,C12530
C5,C_0402,1,4.7uF,C23733
D1,SOD-123_L2.8-W1.8-LS3.7-RD,1,1N4148W,
D2,LED-SMD_4P-L1.6-W1.6-19-237A-BHR6GHC-A01-2T,1,19-237/R6GHBHC-A01/2T,
"D3, D4, D5",D_SOD-323,3,1N4148WS,C2128
J1,AUDIO-SMD_PJ-320B,1,Oscilloscope Jack,
J2,AUDIO-SMD_PJ-320B,1,Axon Output,
J3,AUDIO-SMD_PJ-320B,1,Syn1 Input,
J4,AUDIO-SMD_PJ-320B,1,Syn2 Input,
J5,AUDIO-SMD_PJ-320B,1,Syn3 Input,
J6,AUDIO-SMD_PJ-320B,1,Syn4 Input,
"Q1, Q16, Q17, Q18, Q19, Q2, Q20, Q3, Q6, Q7",SOT-23,10,N_MOSFET,C10488
"Q10, Q11, Q12, Q9",SOT-363-6_L2.0-W1.3-P0.65-LS2.1-BL,4,SI1926DL-T1-E3,
"Q13, Q14",Q_SOT-23,2,MMBT2222A,C7420351
Q15,SOT-23,1,MMBT3904,
"Q4, Q5",SOT-23,2,P_MOSFET,C10487
Q8,TSOP-6_L3.0-W1.5-P0.95-BL,1,SI3552DV-T1-E3,
R1,R_0402,1,6.8kΩ,C25917
"R10, R12, R14, R19, R21, R24, R28, R29, R30, R40, R44, R48, R52, R59, R65, R66, R68, R70, R72, R76, R79, R80, R83, R86, R89, R92",R_0402,26,100kΩ,C25741
"R11, R13, R67, R69, R71, R73, R74, R75, R77, R78, R81, R84, R87, R90, R93",R_0402,15,1MΩ,C26083
"R15, R18, R22, R23, R31, R32, R33, R36, R9",R_0402,9,22kΩ,C25768
R16,R_0402,1,1Ω,C25086
R17,R_0402,1,27kΩ,C25771
"R2, R3",R_0402,2,1kΩ,C11702
"R20, R55",R_0402,2,4.7kΩ,C25900
"R25, R26, R27, R39, R41, R42, R43, R45, R46, R47, R49, R50, R51, R53, R54",R_0402,15,100Ω,C25076
"R34, R35, R6",R_0402,3,47kΩ,C25792
"R37, R38",R_0402,2,2.4kΩ,C25882
R4,R_0402,1,2kΩ,C4109
"R5, R56, R57, R58, R7",R_0402,5,220kΩ,C25767
"R60, R62, R63, R8",R_0402,4,10kΩ,C25744
R61,R_0402,1,300kΩ,C25774
R64,R_0402,1,220Ω,C25091
"R82, R85, R88, R91, R94",R_0402,5,10Ω,C25077
"RV1, RV5, RV6, RV7, RV8",RES-ADJ-SMD_G43BT,5,100kΩ,
"RV2, RV3, RV9",RES-ADJ-SMD_G43BT,3,50kΩ,
RV4,RES-ADJ-SMD_G43BT,1,10kΩ,
SW1,SW-SMD_SSAJ120100,1,SW_SPDT,C160864
"U1, U2, U3",TSSOP-14_L5.0-W4.4-P0.65-LS6.4-BL,3,MCP6004T-I/ST,
"U4, U5, U6",TSSOP-14_L5.0-W4.4-P0.65-LS6.4-BL,3,LM339,C42184

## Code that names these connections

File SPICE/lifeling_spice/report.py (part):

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        "",
    ]
    for item in findings:
        if item.identifier.startswith(("pinmap.", "topology.rv4", "topology.peak_window", "topology.stimulus", "topology.u6b", "naming.stimulus", "power.boost")):
            result = "PASS" if item.passed else ("WARNING" if item.severity == "warning" else "FAIL")
            lines += [f"### {item.summary}", "", f"**{result}.** {item.evidence}", ""]

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        "|---|---|---|---|",
        "| Full operating transient | Integrate, threshold, AP, peak, reset, adaptation, synapse, outputs | Numeric edge counts, rail ranges, periods and trace CSV | No; functional SPICE correlation only |",
        "| RV4 selector sweep | Confirm one-hot physical comparator/switch selection over five regions | S0–S4 states and effective membrane transient ordering | No |",
        "| U23 stimulus transfer sweep | Confirm gain, polarity, clipping, settling and injection current emerge from U23/R92–R96 | `V_Stim_Drive - [Vm_Int + 0.5(V_Stim_Cmd−VREF)]` error inside linear region | No |",
        "| Peak-window event | Confirm active-high `Peak_Window`, U14/U20 closure and positive external pulse | event timing and polarity | No |",
        "| Cold and low-battery startup | Check reference, comparator and boost startup under source impedance | startup time, rail sag, failure mode | No battery-life or safety claim |",
        "| Synapse sign and decay sweeps | Confirm midpoint neutrality, excitatory/inhibitory polarity and RV5 decay | differential Vm response and state decay | No |",
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
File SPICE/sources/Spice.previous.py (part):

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    add_diode(lines, "D2_VM_HIGH", "Vm_Int", "VDD", "BAT54_FALLBACK", "D2 high clamp: Vm_Int -> VDD")
    add_diode(lines, "D3_VM_LOW", "GNDREF", "Vm_Int", "BAT54_FALLBACK", "D3 low clamp: GNDREF -> Vm_Int")

    # Adaptation and spike-pulse shaping diodes.
    add_diode(lines, "D4_VKICK_LOW", "GNDREF", "/Vkick", "D1N4148_FALLBACK", "D4 clamps negative /Vkick")
    add_diode(lines, "D5_VKICK_TO_VW", "/Vkick", "Vw", "D1N4148_FALLBACK", "D5 /Vkick -> Vw")
    add_diode(lines, "D6_ADAPT_TO_VW", "Net-(D6-A)", "Vw", "RB521S30_FALLBACK", "D6 Schottky adaptation injection")
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    plt.figure(figsize=(13, 5))
    plotted = False
    if "Vm_Int" in df:
        plt.plot(t_ms, df["Vm_Int"].to_numpy(), label="Vm_Int", linewidth=2.2)
        plotted = True
    if "Vm_Ext" in df:
        plt.plot(t_ms, df["Vm_Ext"].to_numpy(), label="Vm_Ext", linewidth=2.4)
        plotted = True
    if not plotted:
        plt.plot(t_ms, np.zeros_like(t_ms), label="Vm traces not saved")
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
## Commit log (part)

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2025-08-28 Create LICENSE
2025-08-28 create PCB
2025-08-28 update PCB
2025-10-29 update Images
2026-05-09 PCB update
2026-06-04 create SPICE
2026-06-11 project restructure
2026-06-11 Rename Spiky to LIFeling in README
2026-06-11 update SPICE README
2026-06-14 update Oscilloscope PCB
2026-06-14 update LIFeling PCB
2026-06-19 update PCB for oscilloscope
2026-06-19 update LIFelingPCB
2026-06-24 update pcb oscilloscope
